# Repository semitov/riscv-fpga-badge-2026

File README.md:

# RISC-V Summit Europe 2026 Badge

Electronic badge PCB for RISC-V Summit Europe 2026 in Bologna, Italy. Designed in KiCad 10.

## Available firmware
* [pico2-editor](https://github.com/semitov/pico2-editor), assembly code editor/uploader firmware
* [riscv-badge-displaylib](https://github.com/semitov/riscv-badge-displaylib), display library firmware with several examples

## Gallery

- Render of the badge on KiCad

## License and credits
Designed by: [Tan Siret Akıncı](https://github.com/tansiret), [Emanuele De Paoli](https://github.com/Irdyad), [Carlo Bendelli](https://github.com/CALIOSTRO7), [Valerio Donnini](https://github.com/Valerio-Donnini) and [Alessandro Bocchino](https://github.com/AleB-04).
This open source hardware project is licensed with [CERN-OHL-W](LICENSE). The project is sponsored by © 2026 [RISC-V International](), [NextPCB](https://www.nextpcb.com/), [GOWIN Semiconductor](https://www.gowinsemi.com/en/) and  [DeepComputing](https://deepcomputing.io/).
The project has been certified by [OSHWA](https://oshwa.org/) as Open Source Hardware (UID: [IT000028](https://certification.oshwa.org/it000028.html)).
</br>

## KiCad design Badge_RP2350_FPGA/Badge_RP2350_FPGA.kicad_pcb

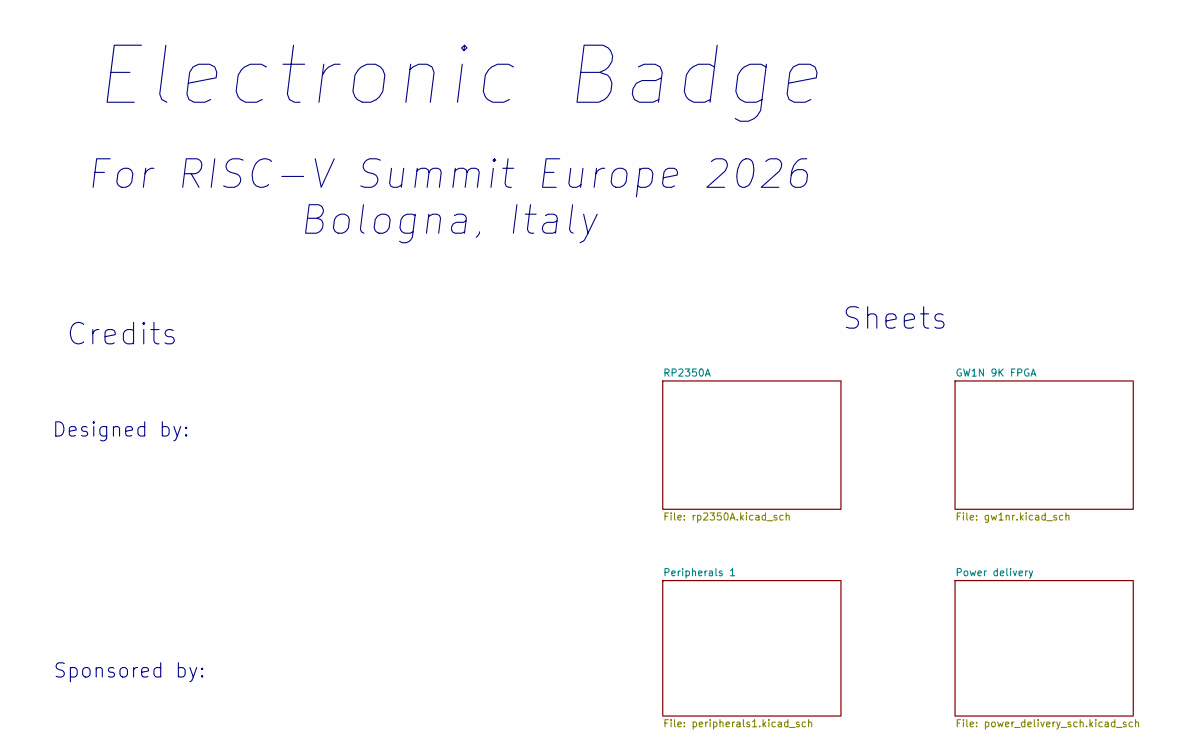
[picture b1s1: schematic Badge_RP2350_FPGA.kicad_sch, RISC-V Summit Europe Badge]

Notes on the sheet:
Sheets
Credits
Electronic Badge
Sponsored by:
For RISC-V Summit Europe 2026 Bologna, Italy
Designed by:

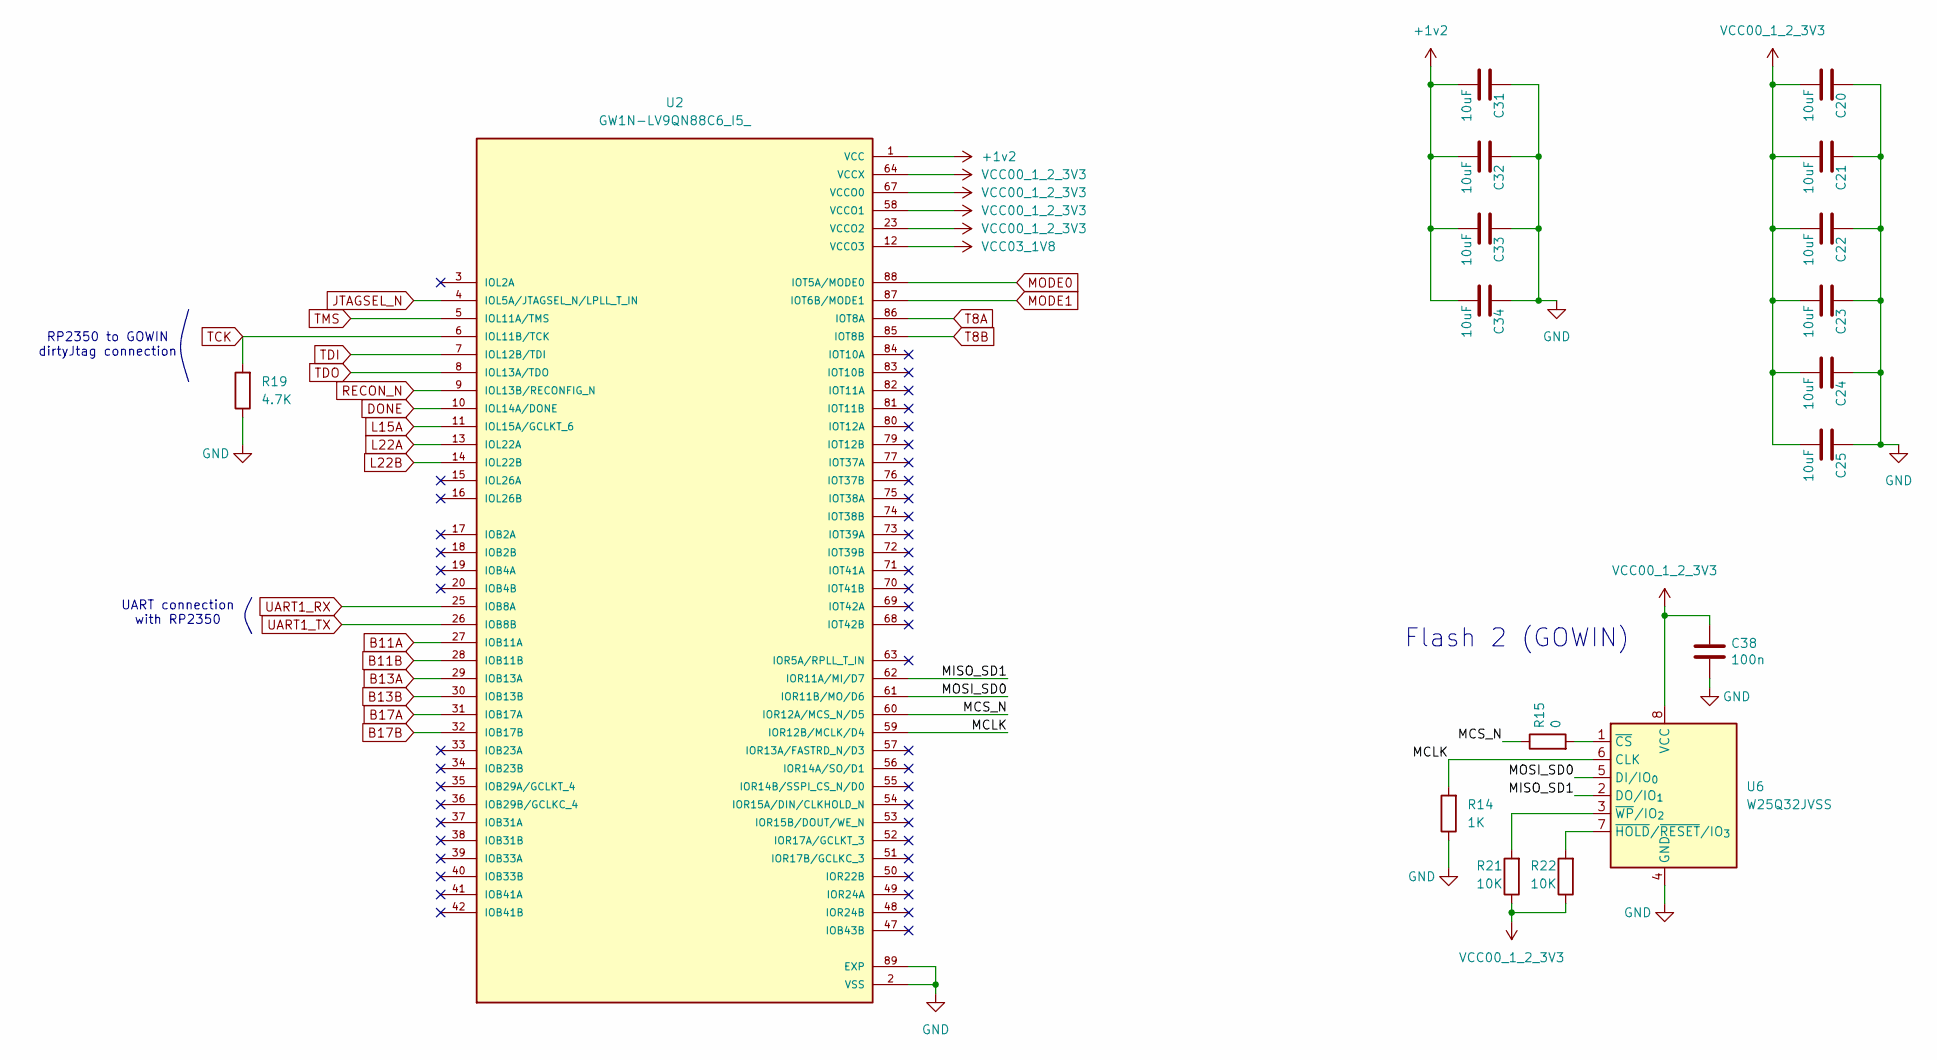
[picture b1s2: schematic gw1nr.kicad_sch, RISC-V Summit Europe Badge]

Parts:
C20, C21, C22, C23, C24, C25, C31, C32, C33, C34: 10uF; C_0402_1005Metric
C38: 100n; C_0402_1005Metric
R14: 1K; R_0402_1005Metric
R15: 0; R_0402_1005Metric
R19: 4.7K; R_0402_1005Metric
R21, R22: 10K; R_0402_1005Metric
U2: GW1N-LV9QN88C6_I5_; ArtInChip_QFN-88-1EP_10x10mm_P0.4mm_EP6.74x6.74mm_ThermalVi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; PARTREV UG103-2.3E
U6: W25Q32JVSS; SOIC-8_5.3x5.3mm_P1.27mm

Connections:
+1v2: C31.2, C32.2, C33.2, C34.2, U2.1 (VCC), U2.22 (VCC), U2.45 (VCC), U2.66 (VCC); also elsewhere on the board
/GW1N 9K FPGA/MCLK: R14.2, U2.59 (IOR12B/MCLK/D4), U6.6 (CLK)
/GW1N 9K FPGA/MCS_N: R15.1, U2.60 (IOR12A/MCS_N/D5)
/GW1N 9K FPGA/MISO_SD1: U2.62 (IOR11A/MI/D7), U6.2 (DO/IO_{1})
/GW1N 9K FPGA/MOSI_SD0: U2.61 (IOR11B/MO/D6), U6.5 (DI/IO_{0})
B11A: U2.27 (IOB11A); also elsewhere on the board
B11B: U2.28 (IOB11B); also elsewhere on the board
B13A: U2.29 (IOB13A); also elsewhere on the board
B13B: U2.30 (IOB13B); also elsewhere on the board
B17A: U2.31 (IOB17A); also elsewhere on the board
B17B: U2.32 (IOB17B); also elsewhere on the board
DONE: U2.10 (IOL14A/DONE); also elsewhere on the board
GND: C20.1, C21.1, C22.1, C23.1, C24.1, C25.1, C31.1, C32.1, C33.1, C34.1, C38.2, R14.1, R19.1, U2.2 (VSS), U2.21 (VSS), U2.24 (VSS), U2.43 (VSS), U2.46 (VSS), U2.65 (VSS), U2.89 (EXP), U6.4 (GND); also elsewhere on the board
JTAGSEL_N: U2.4 (IOL5A/JTAGSEL_N/LPLL_T_IN); also elsewhere on the board
L15A: U2.11 (IOL15A/GCLKT_6); also elsewhere on the board
L22A: U2.13 (IOL22A); also elsewhere on the board
L22B: U2.14 (IOL22B); also elsewhere on the board
MODE0: U2.88 (IOT5A/MODE0); also elsewhere on the board
MODE1: U2.87 (IOT6B/MODE1); also elsewhere on the board
unnamed: R15.2, U6.1 (~CS)
unnamed: R22.2, U6.7 (~HOLD/~RESET/IO_{3})
unnamed: R21.2, U6.3 (~WP/IO_{2})
RECON_N: U2.9 (IOL13B/RECONFIG_N); also elsewhere on the board
TCK: R19.2, U2.6 (IOL11B/TCK); also elsewhere on the board
TDI: U2.7 (IOL12B/TDI); also elsewhere on the board
TDO: U2.8 (IOL13A/TDO); also elsewhere on the board
TMS: U2.5 (IOL11A/TMS); also elsewhere on the board
UART1_RX: U2.25 (IOB8A); also elsewhere on the board
UART1_TX: U2.26 (IOB8B); also elsewhere on the board
VCC00_1_2_3V3: C20.2, C21.2, C22.2, C23.2, C24.2, C25.2, C38.1, R21.1, R22.1, U2.23 (VCCO2), U2.44 (VCCO2), U2.58 (VCCO1), U2.64 (VCCX), U2.67 (VCCO0), U2.78 (VCCX), U6.8 (VCC); also elsewhere on the board
VCC03_1V8: U2.12 (VCCO3); also elsewhere on the board

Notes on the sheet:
RP2350 to GOWIN dirtyJtag connection
UART connection with RP2350
Flash 2 (GOWIN)

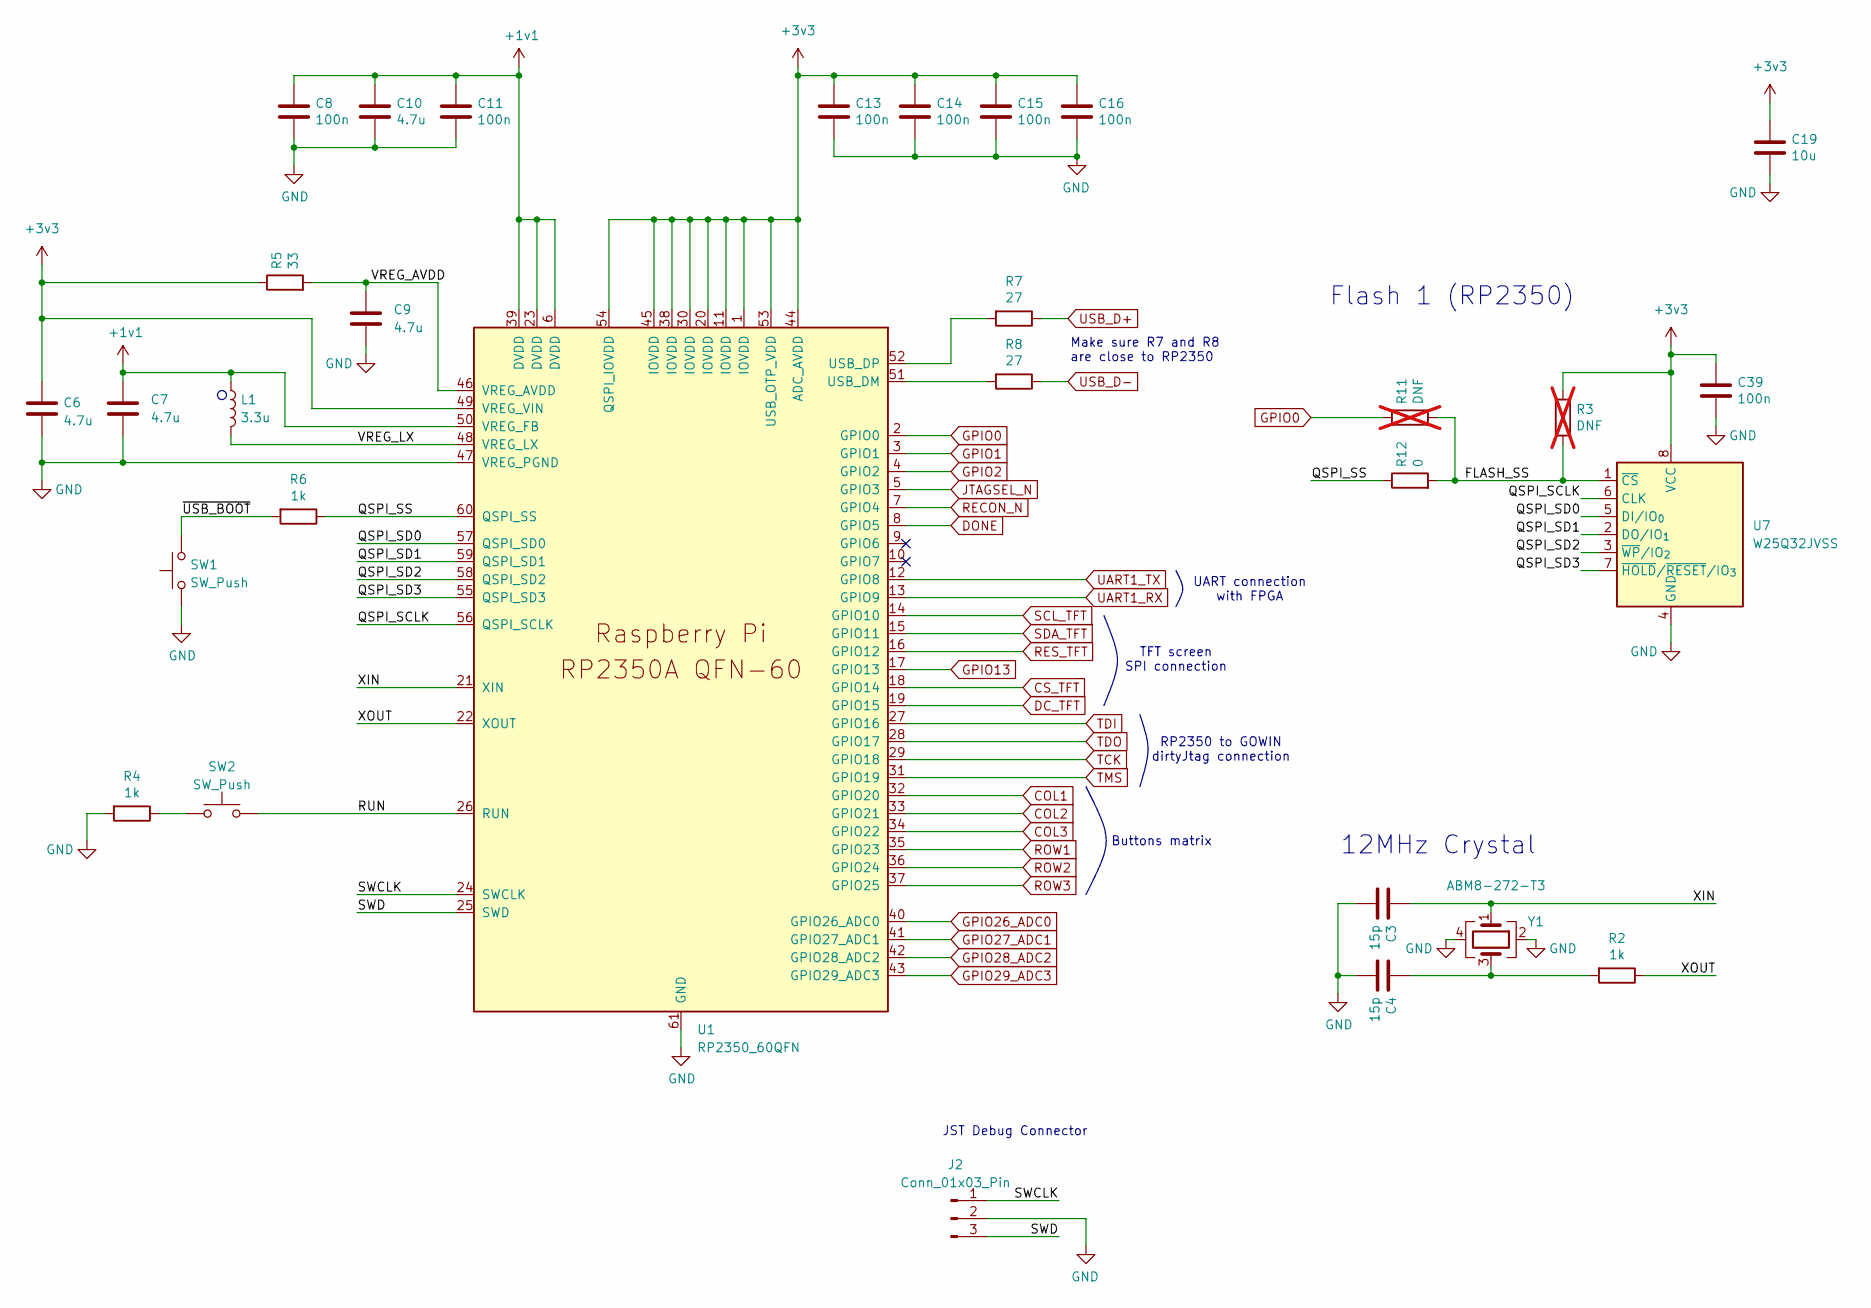
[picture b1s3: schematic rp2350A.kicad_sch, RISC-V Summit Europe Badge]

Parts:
C3, C4: 15p; C_0402_1005Metric
C6, C7, C9, C10: 4.7u; C_0402_1005Metric
C8, C11, C13, C14, C15, C16, C39: 100n; C_0402_1005Metric
C19: 10u; C_0805_2012Metric
J2: Conn_01x03_Pin; PinHeader_1x03_P2.54mm_Vertical
L1: 3.3u; L_pol_2016
R2, R4, R6: 1k; R_0402_1005Metric
R3, R11: DNF; R_0402_1005Metric; not fitted
R5: 33; R_0402_1005Metric
R7, R8: 27; R_0402_1005Metric
R12: 0; R_0402_1005Metric
SW1, SW2: SW_Push; C&K KMR621NGLFS
U1: RP2350_60QFN; RP2350-QFN-60-1EP_7x7_P0.4mm_EP3.4x3.4mm_ThermalVias
U7: W25Q32JVSS; SOIC-8_5.3x5.3mm_P1.27mm
Y1: ABM8-272-T3; Crystal_SMD_3225-4Pin_3.2x2.5mm

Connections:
+1v1: C7.1, C8.1, C10.1, C11.1, L1.1, U1.6 (DVDD), U1.23 (DVDD), U1.39 (DVDD), U1.50 (VREG_FB)
+3v3: C6.1, C13.1, C14.1, C15.1, C16.1, C19.1, C39.1, R3.1, R5.1, U1.1 (IOVDD), U1.11 (IOVDD), U1.20 (IOVDD), U1.30 (IOVDD), U1.38 (IOVDD), U1.44 (ADC_AVDD), U1.45 (IOVDD), U1.49 (VREG_VIN), U1.53 (USB_OTP_VDD), U1.54 (QSPI_IOVDD), U7.8 (VCC); also elsewhere on the board
/RP2350A/FLASH_SS: R3.2, R11.2, R12.2, U7.1 (~CS)
/RP2350A/QSPI_SCLK: U1.56 (QSPI_SCLK), U7.6 (CLK)
/RP2350A/QSPI_SD0: U1.57 (QSPI_SD0), U7.5 (DI/IO_{0})
/RP2350A/QSPI_SD1: U1.59 (QSPI_SD1), U7.2 (DO/IO_{1})
/RP2350A/QSPI_SD2: U1.58 (QSPI_SD2), U7.3 (~WP/IO_{2})
/RP2350A/QSPI_SD3: U1.55 (QSPI_SD3), U7.7 (~HOLD/~RESET/IO_{3})
/RP2350A/QSPI_SS: R6.1, R12.1, U1.60 (QSPI_SS)
/RP2350A/RUN: SW2.2, U1.26 (RUN)
/RP2350A/SWCLK: J2.1, U1.24 (SWCLK)
/RP2350A/SWD: J2.3, U1.25 (SWD)
/RP2350A/VREG_AVDD: C9.1, R5.2, U1.46 (VREG_AVDD)
/RP2350A/VREG_LX: L1.2, U1.48 (VREG_LX)
/RP2350A/XIN: C3.1, U1.21 (XIN), Y1.1
/RP2350A/XOUT: R2.1, U1.22 (XOUT)
/RP2350A/~USB_BOOT: R6.2, SW1.2
COL1: U1.32 (GPIO20); also elsewhere on the board
COL2: U1.33 (GPIO21); also elsewhere on the board
COL3: U1.34 (GPIO22); also elsewhere on the board
CS_TFT: U1.18 (GPIO14); also elsewhere on the board
DC_TFT: U1.19 (GPIO15); also elsewhere on the board
DONE: U1.8 (GPIO5); also elsewhere on the board
GND: C3.2, C4.2, C6.2, C7.2, C8.2, C9.2, C10.2, C11.2, C13.2, C14.2, C15.2, C16.2, C19.2, C39.2, J2.2, R4.2, SW1.1, U1.47 (VREG_PGND), U1.61 (GND), U7.4 (GND), Y1.2, Y1.4; also elsewhere on the board
GPIO0: R11.1, U1.2 (GPIO0); also elsewhere on the board
GPIO1: U1.3 (GPIO1)
GPIO2: U1.4 (GPIO2)
GPIO13: U1.17 (GPIO13)
GPIO26_ADC0: U1.40 (GPIO26_ADC0); also elsewhere on the board
GPIO27_ADC1: U1.41 (GPIO27_ADC1); also elsewhere on the board
GPIO28_ADC2: U1.42 (GPIO28_ADC2); also elsewhere on the board
GPIO29_ADC3: U1.43 (GPIO29_ADC3); also elsewhere on the board
JTAGSEL_N: U1.5 (GPIO3); also elsewhere on the board
unnamed: C4.1, R2.2, Y1.3
unnamed: R4.1, SW2.1
unnamed: R8.2, U1.51 (USB_DM)
unnamed: R7.2, U1.52 (USB_DP)
RECON_N: U1.7 (GPIO4); also elsewhere on the board
RES_TFT: U1.16 (GPIO12); also elsewhere on the board
ROW1: U1.35 (GPIO23); also elsewhere on the board
ROW2: U1.36 (GPIO24); also elsewhere on the board
ROW3: U1.37 (GPIO25); also elsewhere on the board
SCL_TFT: U1.14 (GPIO10); also elsewhere on the board
SDA_TFT: U1.15 (GPIO11); also elsewhere on the board
TCK: U1.29 (GPIO18); also elsewhere on the board
TDI: U1.27 (GPIO16); also elsewhere on the board
TDO: U1.28 (GPIO17); also elsewhere on the board
TMS: U1.31 (GPIO19); also elsewhere on the board
UART1_RX: U1.13 (GPIO9); also elsewhere on the board
UART1_TX: U1.12 (GPIO8); also elsewhere on the board
USB_D+: R7.1; also elsewhere on the board
USB_D-: R8.1; also elsewhere on the board

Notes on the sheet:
Flash 1 (RP2350)
JST Debug Connector
Make sure R7 and R8 are close to RP2350
TFT screen SPI connection
UART connection with FPGA
Buttons matrix
RP2350 to GOWIN dirtyJtag connection
12MHz Crystal

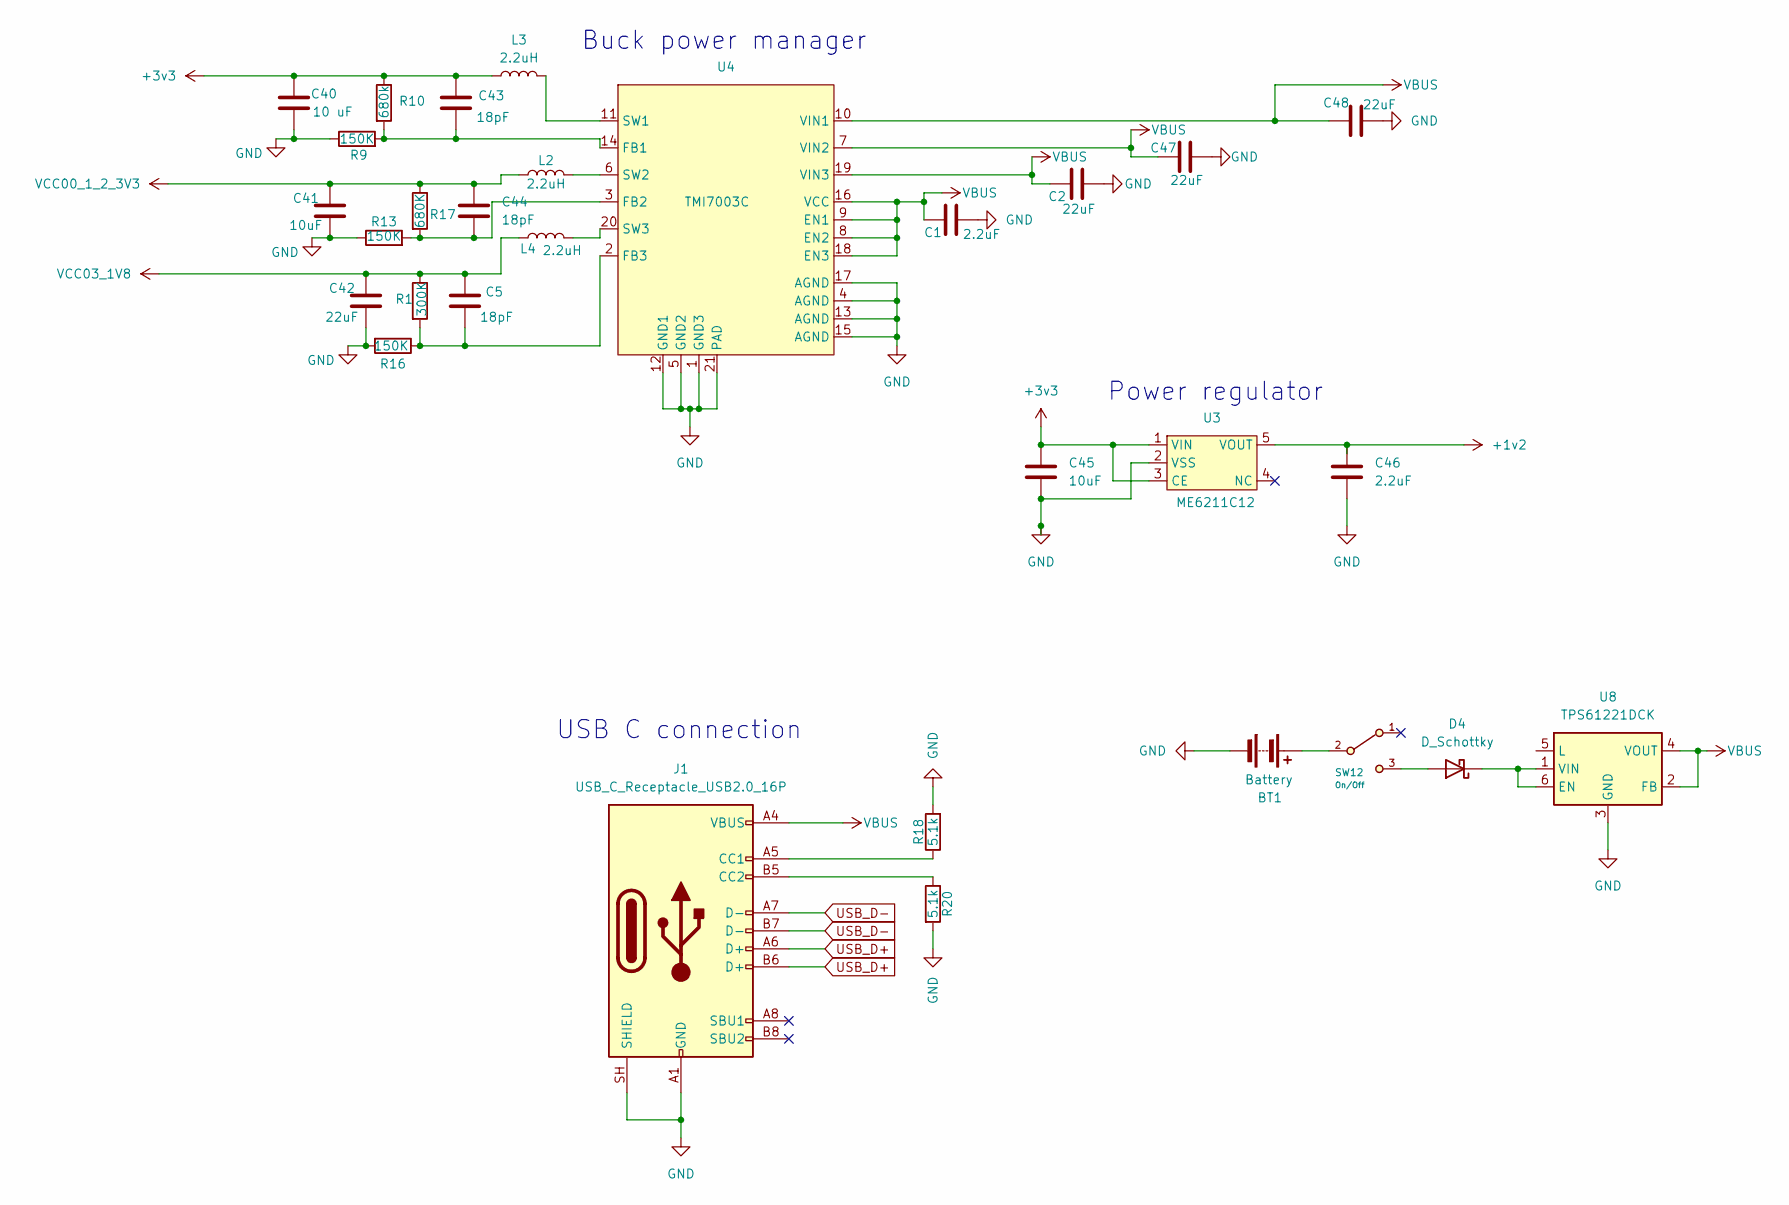
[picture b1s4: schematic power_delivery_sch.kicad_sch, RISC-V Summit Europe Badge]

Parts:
BT1: Battery; BatteryHolder_Keystone_2462_2xAA
C1, C46: 2.2uF; C_0402_1005Metric
C2, C42, C47, C48: 22uF; C_0402_1005Metric
C5, C43, C44: 18pF; C_0402_1005Metric
C40: 10 uF; C_0402_1005Metric
C41, C45: 10uF; C_0402_1005Metric
D4: D_Schottky; D_SOD-123
J1: USB_C_Receptacle_USB2.0_16P; USB_C_Receptacle_HRO_TYPE-C-31-M-12
L2, L3, L4: 2.2uH; L_APV_ANR4018
R1: 300K; R_0402_1005Metric
R9, R13, R16: 150K; R_0402_1005Metric
R10: 680k; R_0402_1005Metric
R17: 680K; R_0402_1005Metric
R18, R20: 5.1k; R_0402_1005Metric
SW12: On/Off; C&K JS102011SAQN
U3: ME6211C12; SOT-23-5_L3.0-W1.7-P0.95-LS2.8-BL
U4: TMI7003C; QFN-20_L3.0-W3.0-P0.40-BL-EP1.7
U8: TPS61221DCK; Texas_R-PDSO-G6

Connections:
+1v2: C46.1, U3.5 (VOUT); also elsewhere on the board
+3v3: C40.1, C43.1, C45.1, L3.1, R10.1, U3.1 (VIN), U3.3 (CE); also elsewhere on the board
GND: BT1.2 (-), C1.2, C2.2, C40.2, C41.2, C42.2, C45.2, C46.2, C47.2, C48.2, J1.A1 (GND), J1.A12 (GND), J1.B1 (GND), J1.B12 (GND), J1.SH (SHIELD), R9.1, R13.1, R16.2, R18.2, R20.2, U3.2 (VSS), U4.1 (GND3), U4.4 (AGND), U4.5 (GND2), U4.12 (GND1), U4.13 (AGND), U4.15 (AGND), U4.17 (AGND), U4.21 (PAD), U8.3 (GND); also elsewhere on the board
unnamed: BT1.1 (+), SW12.2 (B)
unnamed: D4.2 (A), SW12.3 (C)
unnamed: D4.1 (K), U8.1 (VIN), U8.6 (EN)
unnamed: J1.A5 (CC1), R18.1
unnamed: J1.B5 (CC2), R20.1
unnamed: C43.2, R9.2, R10.2, U4.14 (FB1)
unnamed: C44.2, R13.2, R17.2, U4.3 (FB2)
unnamed: C5.2, R1.2, R16.1, U4.2 (FB3)
unnamed: L3.2, U4.11 (SW1)
unnamed: L2.2, U4.6 (SW2)
unnamed: L4.2, U4.20 (SW3)
USB_D+: J1.A6 (D+), J1.B6 (D+); also elsewhere on the board
USB_D-: J1.A7 (D-), J1.B7 (D-); also elsewhere on the board
VBUS: C1.1, C2.1, C47.1, C48.1, J1.A4 (VBUS), J1.A9 (VBUS), J1.B4 (VBUS), J1.B9 (VBUS), U4.7 (VIN2), U4.8 (EN2), U4.9 (EN1), U4.10 (VIN1), U4.16 (VCC), U4.18 (EN3), U4.19 (VIN3), U8.2 (FB), U8.4 (VOUT)
VCC00_1_2_3V3: C41.1, C44.1, L2.1, R17.1; also elsewhere on the board
VCC03_1V8: C5.1, C42.1, L4.1, R1.1; also elsewhere on the board

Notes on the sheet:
Power regulator
USB C connection
Buck power manager

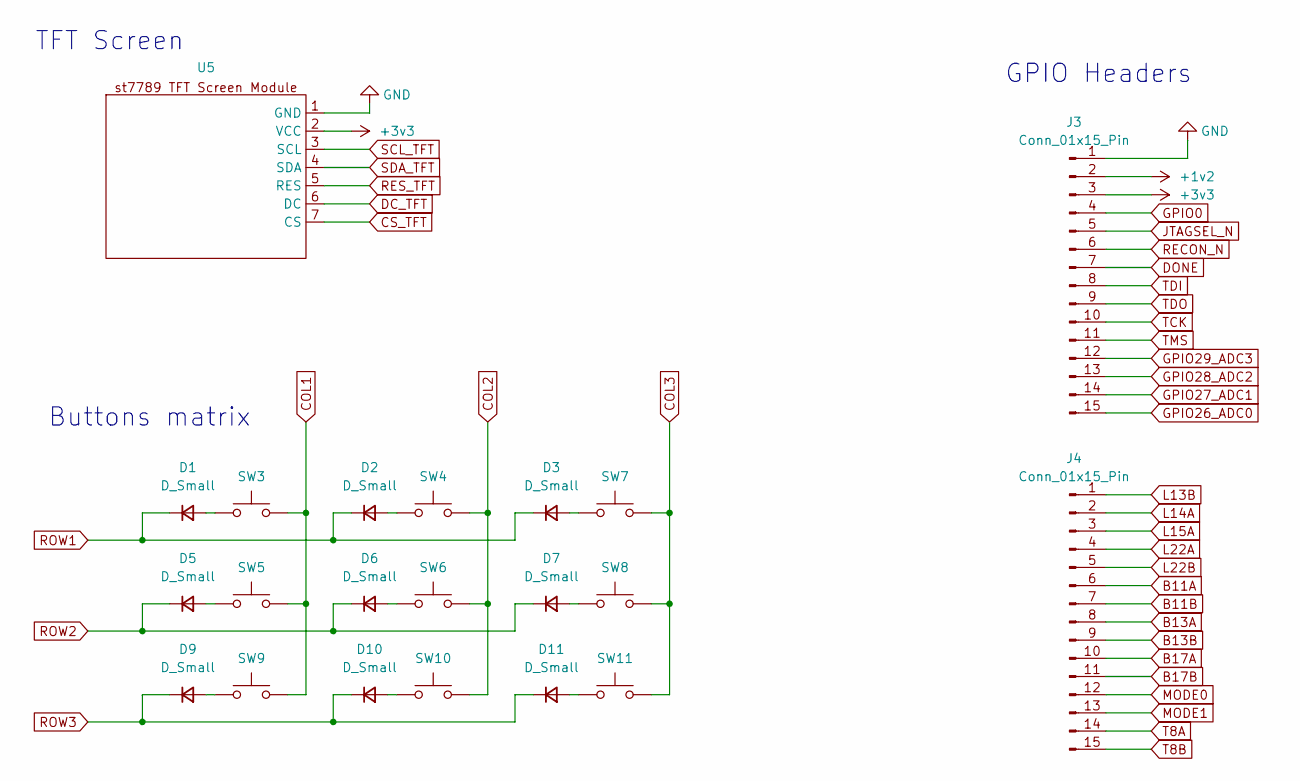
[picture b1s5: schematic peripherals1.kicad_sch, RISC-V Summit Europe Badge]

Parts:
D1, D2, D3, D5, D6, D7, D9, D10, D11: D_Small; Nexperia BAS516,115
J3, J4: Conn_01x15_Pin; PinHeader_1x15_P2.54mm_Vertical
SW3, SW4, SW5, SW6, SW7, SW8, SW9, SW10, SW11: SHOU HAN TS665PA 250gf
U5: st7789_7pin_noblk

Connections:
+1v2: J3.2; also elsewhere on the board
+3v3: J3.3, U5.2 (VCC); also elsewhere on the board
B11A: J4.6; also elsewhere on the board
B11B: J4.7; also elsewhere on the board
B13A: J4.8; also elsewhere on the board
B13B: J4.9; also elsewhere on the board
B17A: J4.10; also elsewhere on the board
B17B: J4.11; also elsewhere on the board
COL1: SW3.2, SW5.2, SW9.2; also elsewhere on the board
COL2: SW4.2, SW6.2, SW10.2; also elsewhere on the board
COL3: SW7.2, SW8.2, SW11.2; also elsewhere on the board
CS_TFT: U5.7 (CS); also elsewhere on the board
DC_TFT: U5.6 (DC); also elsewhere on the board
DONE: J3.7; also elsewhere on the board
GND: J3.1, U5.1 (GND); also elsewhere on the board
GPIO0: J3.4; also elsewhere on the board
GPIO26_ADC0: J3.15; also elsewhere on the board
GPIO27_ADC1: J3.14; also elsewhere on the board
GPIO28_ADC2: J3.13; also elsewhere on the board
GPIO29_ADC3: J3.12; also elsewhere on the board
JTAGSEL_N: J3.5; also elsewhere on the board
L13B: J4.1
L14A: J4.2
L15A: J4.3; also elsewhere on the board
L22A: J4.4; also elsewhere on the board
L22B: J4.5; also elsewhere on the board
MODE0: J4.12; also elsewhere on the board
MODE1: J4.13; also elsewhere on the board
unnamed: D1.2 (A), SW3.1
unnamed: D2.2 (A), SW4.1
unnamed: D3.2 (A), SW7.1
unnamed: D5.2 (A), SW5.1
unnamed: D6.2 (A), SW6.1
unnamed: D7.2 (A), SW8.1
unnamed: D9.2 (A), SW9.1
unnamed: D10.2 (A), SW10.1
unnamed: D11.2 (A), SW11.1
RECON_N: J3.6; also elsewhere on the board
RES_TFT: U5.5 (RES); also elsewhere on the board
ROW1: D1.1 (K), D2.1 (K), D3.1 (K); also elsewhere on the board
ROW2: D5.1 (K), D6.1 (K), D7.1 (K); also elsewhere on the board
ROW3: D9.1 (K), D10.1 (K), D11.1 (K); also elsewhere on the board
SCL_TFT: U5.3 (SCL); also elsewhere on the board
SDA_TFT: U5.4 (SDA); also elsewhere on the board
TCK: J3.10; also elsewhere on the board
TDI: J3.8; also elsewhere on the board
TDO: J3.9; also elsewhere on the board
TMS: J3.11; also elsewhere on the board

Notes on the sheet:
Buttons matrix
TFT Screen
GPIO Headers

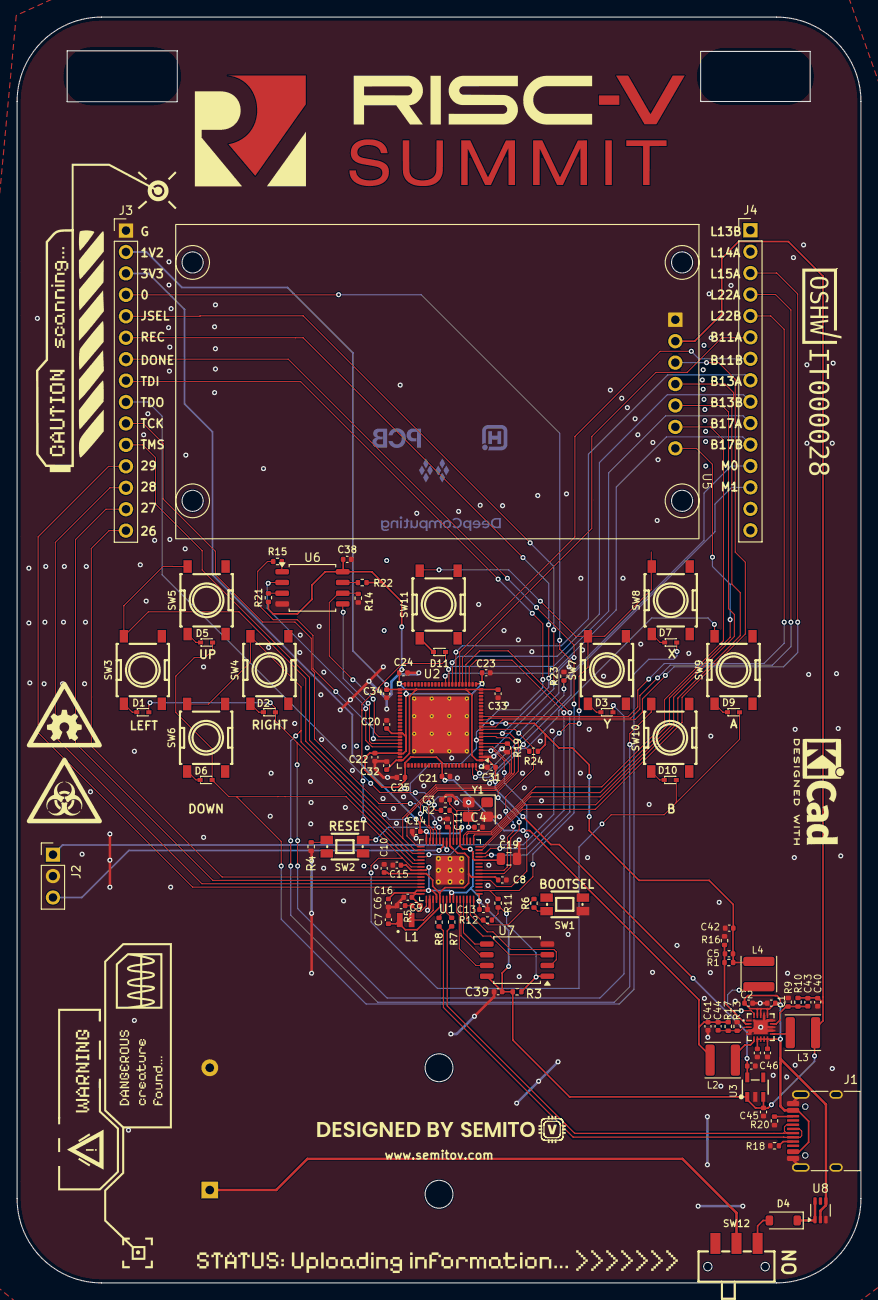
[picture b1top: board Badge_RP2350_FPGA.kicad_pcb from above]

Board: 2 copper layers, 100.0 x 150.0 mm, 101 parts (1 on the bottom side), 91 nets.

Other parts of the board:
R23: 1K; R_0402_1005Metric
R24: 4.7K; R_0402_1005Metric

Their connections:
GND: R23.2; also elsewhere on the board
MODE0: R23.1; also elsewhere on the board
MODE1: R24.2; also elsewhere on the board
VCC03_1V8: R24.1; also elsewhere on the board

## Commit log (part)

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2026-05-21 edit more
2026-05-22 fix a bunch of stuff
2026-06-04 cleanup
2026-06-04 add alternative firmware

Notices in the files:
Badge_RP2350_FPGA/Badge_RP2350_FPGA.kicad_pcb:
License: CERN-OHL-W-2.0
CERN-OHL-W 2.0
